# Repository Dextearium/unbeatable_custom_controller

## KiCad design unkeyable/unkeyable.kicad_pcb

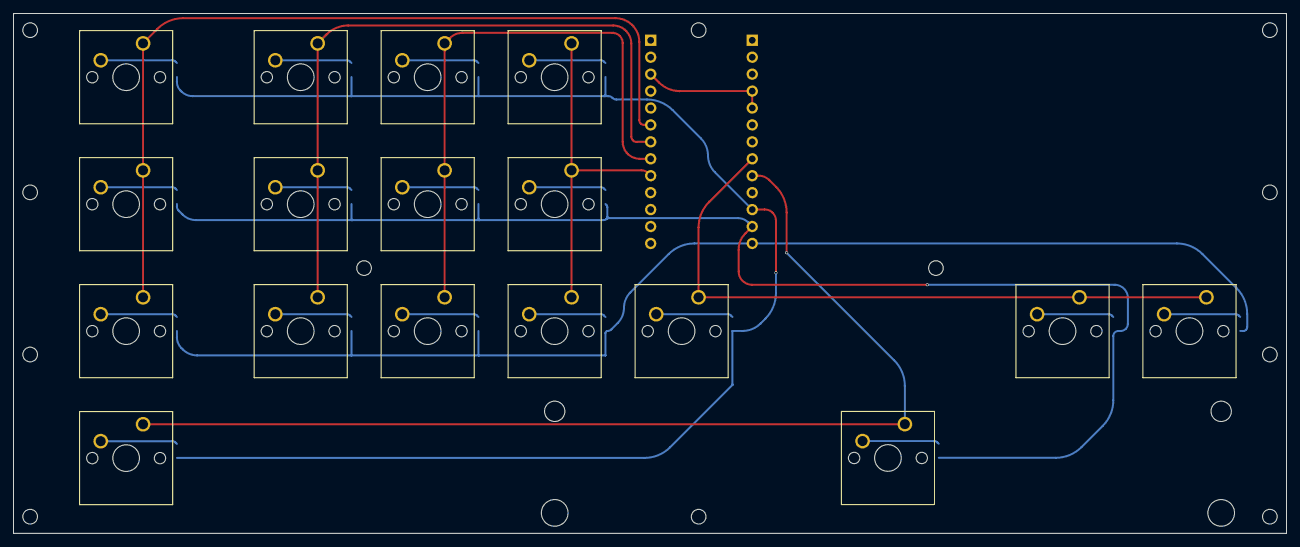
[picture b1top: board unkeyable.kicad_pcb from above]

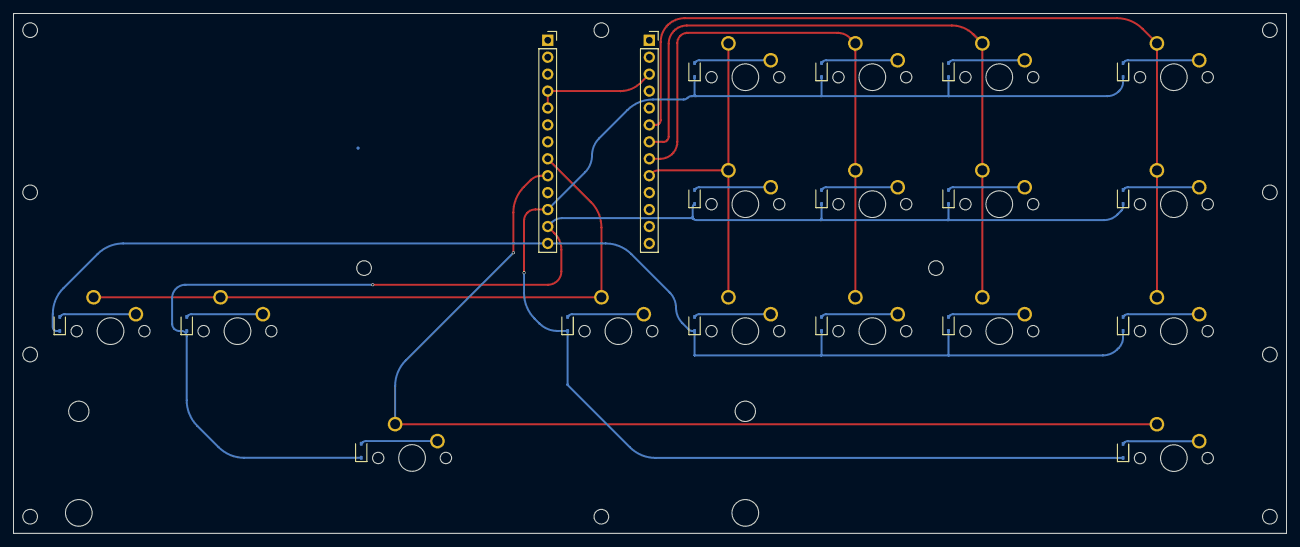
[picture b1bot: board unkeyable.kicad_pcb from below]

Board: 2 copper layers, 191.0 x 78.0 mm, 36 parts (19 on the bottom side), 27 nets.

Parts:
D1, D2, D3, D4, D5, D6, D7, D8, D9, D10, D11, D12, D13, D14, D15, D16, D17: 1n4148; D_SOD-323
J1, J2: Conn_01x13; PinSocket_1x13_P2.54mm_Vertical
SW1: ESC; SW_Cherry_MX_1.75u_PCB
SW2: 1; SW_Cherry_MX_1.00u_PCB
SW3: C; SW_Cherry_MX_1.00u_PCB
SW4: 3; SW_Cherry_MX_1.00u_PCB
SW5: SHIFT; SW_Cherry_MX_1.75u_PCB
SW6: Q; SW_Cherry_MX_1.00u_PCB
SW7: W; SW_Cherry_MX_1.00u_PCB
SW8: E; SW_Cherry_MX_1.00u_PCB
SW9: CTRL; SW_Cherry_MX_1.75u_PCB
SW10: A; SW_Cherry_MX_1.00u_PCB
SW11: S; SW_Cherry_MX_1.00u_PCB
SW12: D; SW_Cherry_MX_1.00u_PCB
SW13: F; SW_Cherry_MX_1.00u_PCB
SW14: J; SW_Cherry_MX_1.00u_PCB
SW15: K; SW_Cherry_MX_1.00u_PCB
SW16: ALT; SW_Cherry_MX_1.75u_PCB
SW17: SPACE; SW_Cherry_MX_6.25u_PCB

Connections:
/RP2040/GPIO4: J1.8, SW13.1, SW14.1, SW15.1
/RP2040/GPIO5: J1.9, SW16.1, SW17.1
/RP2040/GPIO7: D1.1 (K), D2.1 (K), D3.1 (K), D4.1 (K), D13.1 (K), D16.1 (K), J1.11
/RP2040/GPIO8: D5.1 (K), D6.1 (K), D7.1 (K), D8.1 (K), D14.1 (K), D17.1 (K), J1.12
/RP2040/GPIO9: D9.1 (K), D10.1 (K), D11.1 (K), D12.1 (K), D15.1 (K), J1.13
/RP2040/GPIO26_ADC0: J2.9, SW4.1, SW8.1, SW12.1
/RP2040/GPIO27_ADC1: J2.8, SW3.1, SW7.1, SW11.1
/RP2040/GPIO28_ADC2: J2.7, SW2.1, SW6.1, SW10.1
/RP2040/GPIO29_ADC3: J2.6, SW1.1, SW5.1, SW9.1
GND: J1.4, J1.5, J2.3
unnamed: D1.2 (A), SW1.2
unnamed: D2.2 (A), SW2.2
unnamed: D3.2 (A), SW3.2
unnamed: D4.2 (A), SW4.2
unnamed: D5.2 (A), SW5.2
unnamed: D6.2 (A), SW6.2
unnamed: D7.2 (A), SW7.2
unnamed: D8.2 (A), SW8.2
unnamed: D9.2 (A), SW9.2
unnamed: D10.2 (A), SW10.2
unnamed: D11.2 (A), SW11.2
unnamed: D12.2 (A), SW12.2
unnamed: D13.2 (A), SW13.2
unnamed: D14.2 (A), SW14.2
unnamed: D15.2 (A), SW15.2
unnamed: D16.2 (A), SW16.2
unnamed: D17.2 (A), SW17.2

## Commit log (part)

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2026-05-21 started work
2026-05-29 Adding RP2040 minimal viable schematic
2026-06-22 working on Schematics
